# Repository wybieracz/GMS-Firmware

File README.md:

# Grid Management System - Device and Firmware
## IoT class system of electricity management based on a cloud interface
The project involves the design and development of a device that allows remote control the power supply of the connected receiver. Powering the receiver on and off should be possible on demand, after a certain period of time, during designated periods. In addition, the device will conduct measurements of voltage and current and count the energy used (Smart Socket). The second part of the project is creation of a web application to manage the device and present statistics. Communication with the device and data storage will be possible through a configured cloud service.
## Technologies
* C++
* Azure IoT Hub
* Azure Stream Analytics
* ESP-32
## Libraries
* SPIFFS
* LiquidCrystal
* ESPAsyncWebServer
* EmonLib
* Azure IoT device SDK for C
## Device features
* Wi-Fi connection wizzard
* 230V/10A power supply control
* Manual mode, time mode, auto mode
* Programmable display (Voltage and current, date, power, power consumption)
* Power compsumption counter with auto-resetter
* Sending telemetry to cloud
## Circuit idea diagram

## Circuit diagram

## PCB design

## Device case design

## System architecture

The solution consists of six major components:
* IoT Device - smart device able to work in GMS.
* Azure IoT Hub - a managed cloud service that acts as a central message hub for communication between an IoT application and its attached devices.
* Azure Stream Analytics - cloud service that provides real-time analytic computations on the data streaming from IoT devices.
* Azure Database for PostgreSQL - Database used to store devices telemetry and web app data.
* Azure App Service - Web app used for device manipulation and telemetry presentation. [(Backend)](https://github.com/wybieracz/GMS-App)
* Azure Storage Accounts - Web app used for device manipulation and telemetry presentation. [(Frontend)](https://github.com/wybieracz/GMS-App)
## Getting started
1. Create IoT device using circuit diagram / PCB design.
2. Create account on [Microsoft Azure](https://azure.microsoft.com/en-gb/).
3. Create [Azure IoT Hub](https://docs.microsoft.com/en-gb/azure/iot-hub/iot-hub-create-through-portal).
4. In Azure IoT Hub add new device via `Devices > Add Device`.
5. Clone repository.
6. Open `AzIoTConfig.h` file.
* In Azure IoT Hub open `Overview` to show hostname.
* Enter cloud hostname `IOTHUB_FQDN`.
* In Azure IoT Hub open `Devices > Your Device Name` to show cloud device credentials.
* Enter cloud device credentials, Device ID `DEVICE_ID` and Primary Key `DEVICE_KEY`.
7. Build and upload programme to ESP-32.
8. Create Postgres database.
9. Run [backend](https://github.com/wybieracz/GMS-App) to create entities.
10. Add manually data about devices into devices table.
11. Create and configure Azure Stream Analytics.
* Define Azure IoT Hub as an input in `Inputs > Add input`.
* Define Postgres database as an output in `Outputs > Add output`.
* Define query:
```
SELECT
    [deviceId],
    [voltage],
    [current],
    [power],
    [kWh],
    [timestamp]
INTO
    [database_name]
FROM
    [iot_hub_name]
```
12. Connect power supply to device.
13. Connect to the Wi-Fi network. Credentials will be displayed on device display.
14. Go to `192.168.4.1` and pass credentials to your home Wi-Fi. The device will reboot and connect to the Wi-Fi.
15. Your device is now online and can be linked with your account.
16. For device manipulation check [GMS - App](https://github.com/wybieracz/SZEE-App).
## Device

Device overview.

After device startup it will show Wi-Fi credentials. When connected, it is possible to configure device netowrk settings and connect it to the home Wi-Fi.

After network configuration, device will reboot and connect to the home Wi-Fi.

It is possible to configure data presented on device display. 16x2 LCD allows to display two of data: Time and date, voltage and current, power, power comsumption. In addition it is powwible to change display brightness.
## Video presentation
[YouTube](https://youtu.be/LqCKxmR3ckY)

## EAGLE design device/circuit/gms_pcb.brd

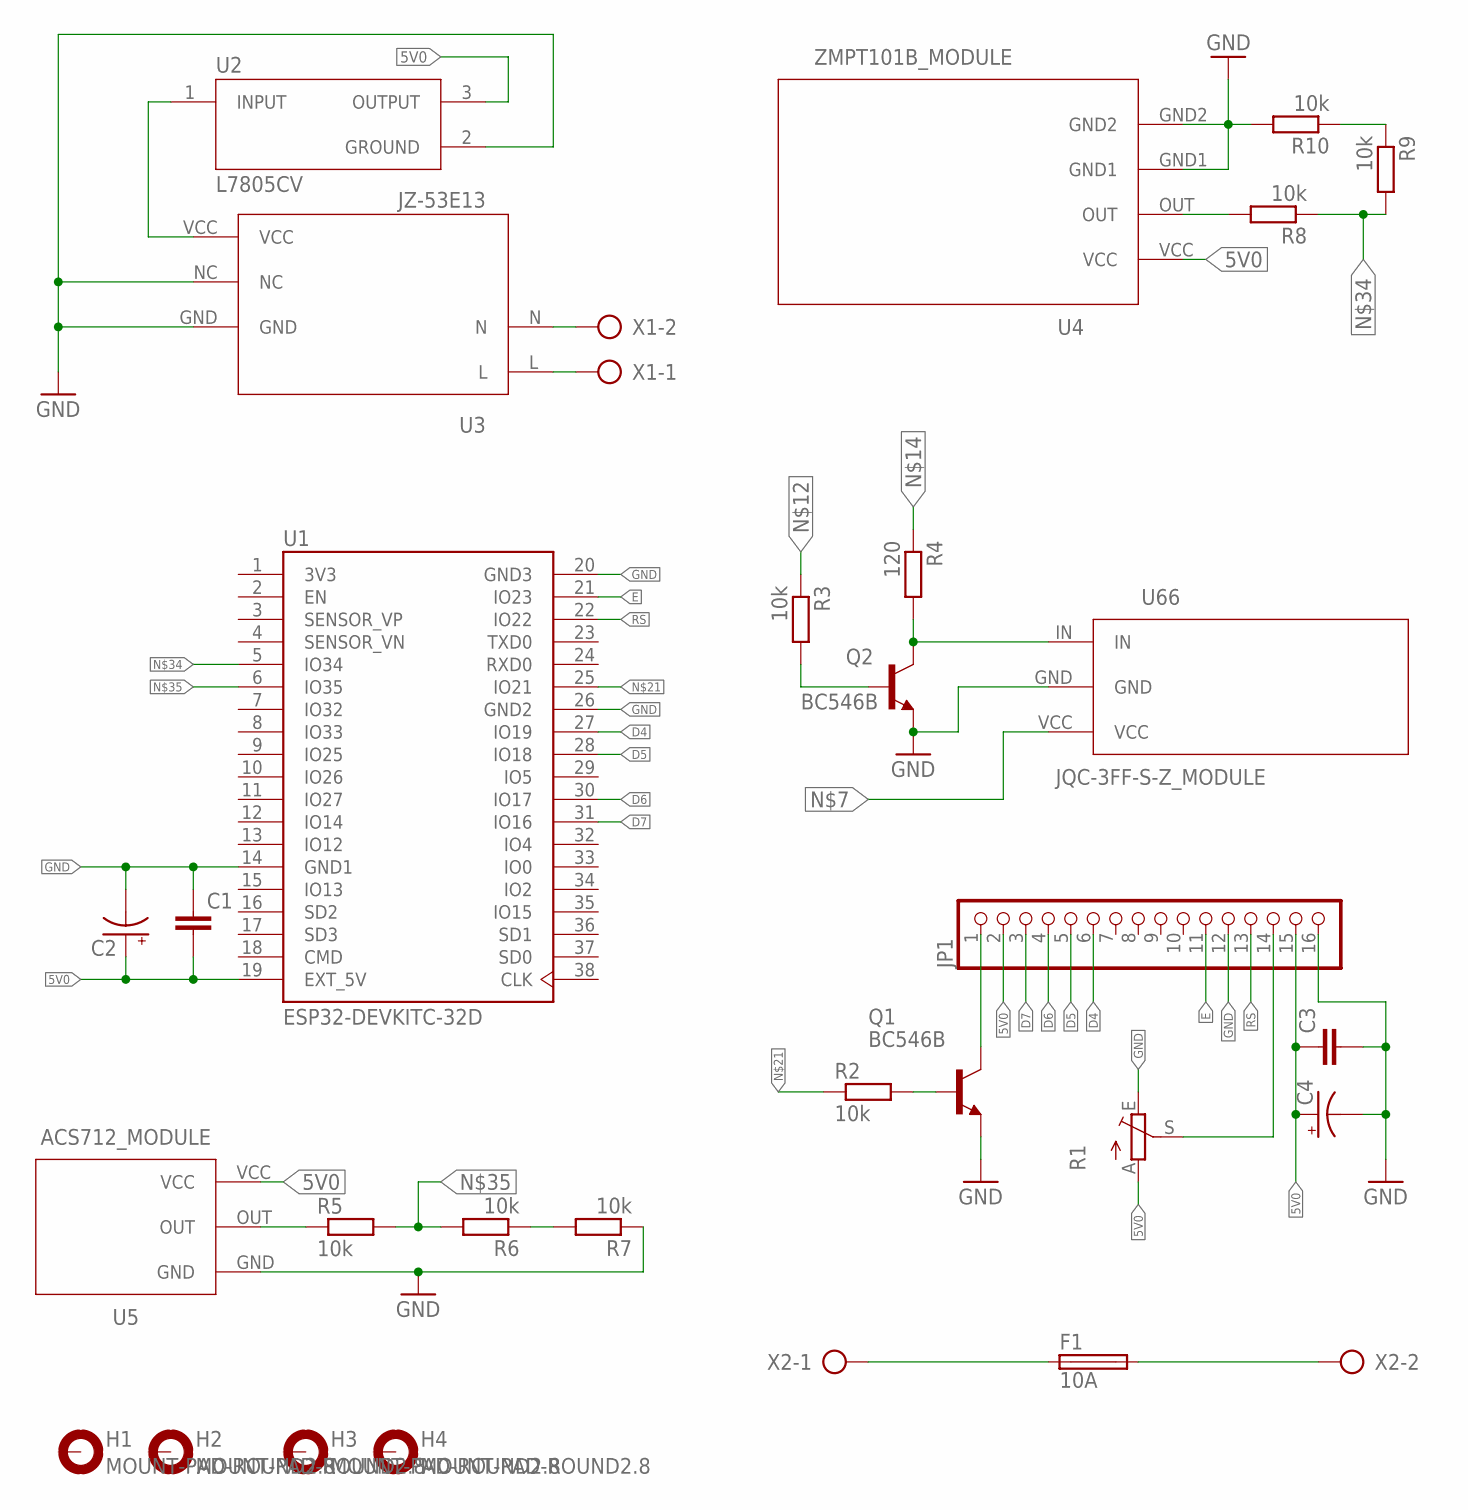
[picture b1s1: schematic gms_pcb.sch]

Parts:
C1, C3: C-EU025-025X050; C025-025X050
C2, C4: CPOL-USE2.5-6; E2,5-6
F1: 10A; SH25
H1, H2, H3, H4: MOUNT-PAD-ROUND2.8; 2,8-PAD
JP1: PINHD-1X16; 1X16
Q1, Q2: BC546B; TO92-EBC
R1: TRIM_EU-CA6V; CA6V
R2, R3, R5, R6, R7, R8, R9, R10: 10k; 0204/7
R4: 120; 0204/7
U1: ESP32-DEVKITC-32D; MODULE_ESP32-DEVKITC-32D
U2: L7805CV; TO255P1040X460X1968-3
U3: JZ-53E13
U4: ZMPT101B_MODULE
U5: ACS712_MODULE
U66: JQC-3FF-S-Z_MODULE; JQC-3FF-S-Z_MOUDLE
X1, X2: AK500/2

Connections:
3V3: U1.1 (3V3)
5V0: C1.2, C2.+, C3.1, C4.+, JP1.2, JP1.15, R1.A, U1.19 (EXT_5V), U2.3 (OUTPUT), U4.VCC, U5.VCC
12V0: U2.1 (INPUT), U3.VCC
D4: JP1.6, U1.27 (IO19)
D5: JP1.5, U1.28 (IO18)
D6: JP1.4, U1.30 (IO17)
D7: JP1.3, U1.31 (IO16)
E: JP1.11, U1.21 (IO23)
GND: C1.1, C2.-, C3.2, C4.-, JP1.12, JP1.16, Q1.E, Q2.E, R1.E, R7.1, R10.2, U1.14 (GND1), U1.20 (GND3), U1.26 (GND2), U2.2 (GROUND), U3.GND, U3.NC, U4.GND1, U4.GND2, U5.GND, U66.GND
L2: F1.1, X2.1
N2: F1.2, X2.2
unnamed: Q2.C, R4.2, U66.IN
unnamed: JP1.14, R1.S
unnamed: R8.2, U4.OUT
unnamed: U3.N, X1.2
unnamed: JP1.1, Q1.C
unnamed: Q1.B, R2.2
unnamed: Q2.B, R3.2
unnamed: R9.1, R10.1
unnamed: R6.1, R7.2
unnamed: U3.L, X1.1
unnamed: R5.1, U5.OUT
unnamed: R2.1, U1.25 (IO21)
unnamed: R8.1, R9.2, U1.5 (IO34)
unnamed: R5.2, R6.2, U1.6 (IO35)
RS: JP1.13, U1.22 (IO22)

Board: 2 copper layers, 30 parts (0 on the bottom side), 25 nets, no tracks yet.

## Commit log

2022-10-08 Added README.md, .gitignore (C++) files
2022-10-08 feature: c2d and d2c messaging
2022-10-29 feature: endable sending telemetry
2022-11-21 feature: wifi manager, flash memory, relay, lcd
2022-11-22 feature: display wifi status on lcd
2022-11-26 feature: read V and I values
2022-11-26 refactor: change style to opp
2022-11-27 feature: customized display
2022-11-27 feature: send telemetry, time mode, auto mode
2022-11-29 feature: return device status
2022-11-30 fix: getStatus fix
2022-11-30 feature: setSettings and setRegistered remote functions
2022-12-07 fix: setRegistered fix and set rules if empty on boot
2022-12-09 fix: payloadBuffer overflow fix
2022-12-10 fix: auto mode in local time
2022-12-17 fix: pinout fix
2022-12-22 fix: energy calculation fix
2023-01-03 fix: unregister device fix
2023-01-09 fix: mothod handler function removal
2023-01-09 feature: rwd in connection page
2023-08-06 docs: add screenshots and photos
2023-08-06 docs: add diagrams
2023-08-06 docs: update README.md
2023-08-06 fix: fix photos links in README.md
2023-08-10 docs: update tech description
